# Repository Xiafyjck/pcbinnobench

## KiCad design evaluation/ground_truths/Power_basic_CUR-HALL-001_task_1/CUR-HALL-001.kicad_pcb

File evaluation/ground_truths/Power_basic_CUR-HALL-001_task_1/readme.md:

# CUR-HALL-001: Hall Effect Current Sensor Front-End Board

Uses ACS712 and OPA333 for current sensing, powered by 5V, but output voltage does not exceed 3.3V, ±20A range.

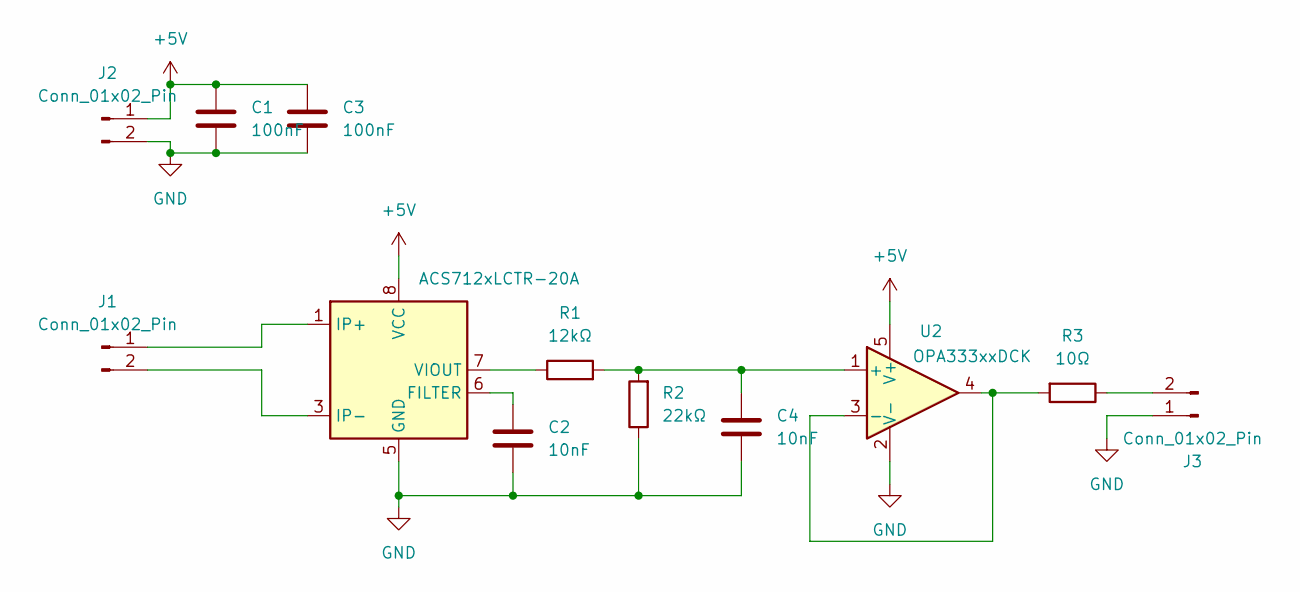
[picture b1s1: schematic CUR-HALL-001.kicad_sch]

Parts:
C1, C3: 100nF; C_0805_2012Metric
C2, C4: 10nF; C_0805_2012Metric
J1: Conn_01x02_Pin; Samtec_HPM-02-01-x-S_Straight_1x02_Pitch5.08mm
J2, J3: Conn_01x02_Pin; JST_EH_B2B-EH-A_1x02_P2.50mm_Vertical
R1: 12kΩ; R_0805_2012Metric
R2: 22kΩ; R_0805_2012Metric
R3: 10Ω; R_0805_2012Metric
U1: ACS712xLCTR-20A; SOIC-8_3.9x4.9mm_P1.27mm
U2: OPA333xxDCK; SOT-353_SC-70-5

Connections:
+5V: C1.1, C3.1, J2.1, U1.8 (VCC), U2.5 (V+)
GND: C1.2, C2.2, C3.2, C4.2, J2.2, J3.1, R2.1, U1.5 (GND), U2.2 (V-)
unnamed: J1.1, U1.1 (IP+), U1.2 (IP+)
unnamed: J1.2, U1.3 (IP-), U1.4 (IP-)
unnamed: J3.2, R3.1
unnamed: C2.1, U1.6 (FILTER)
unnamed: R1.1, U1.7 (VIOUT)
unnamed: C4.1, R1.2, R2.2, U2.1 (+)
unnamed: R3.2, U2.3 (-), U2.4

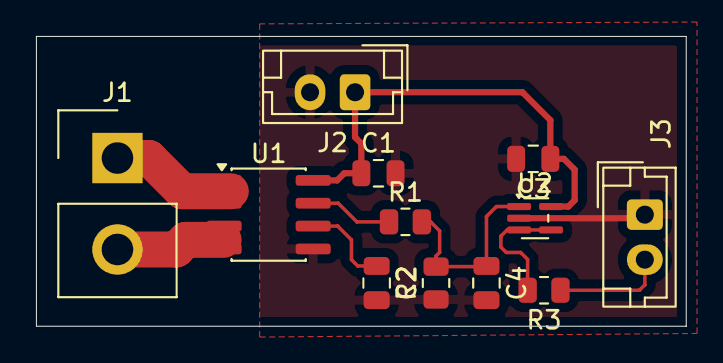
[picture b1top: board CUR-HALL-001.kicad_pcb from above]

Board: 2 copper layers, 36.1 x 16.1 mm, 12 parts (0 on the bottom side), 9 nets.

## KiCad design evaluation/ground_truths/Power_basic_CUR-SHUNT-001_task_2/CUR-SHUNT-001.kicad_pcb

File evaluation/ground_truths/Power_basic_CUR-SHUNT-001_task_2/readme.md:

# INA282 Low-Side Current Sensing

Use INA282 with 1.65V offset for current sensing.

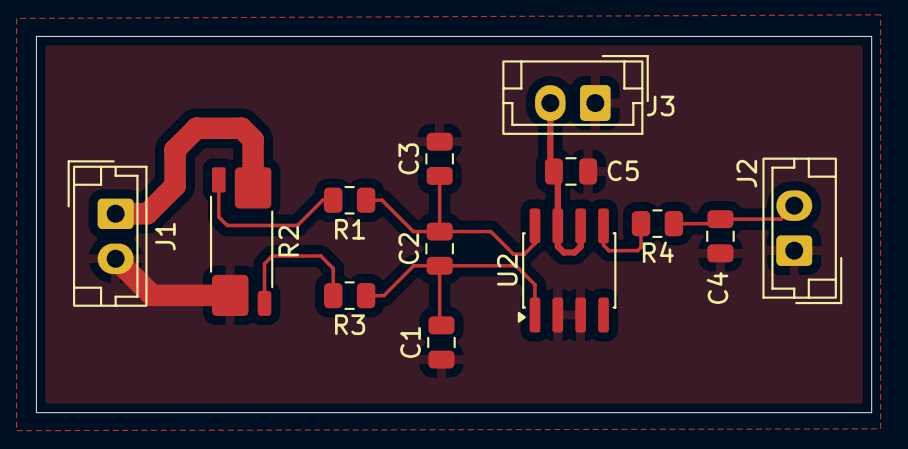
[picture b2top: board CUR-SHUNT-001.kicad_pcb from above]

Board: 2 copper layers, 46.4 x 20.9 mm, 13 parts (0 on the bottom side), 9 nets.

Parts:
C1, C2, C3: NC; C_0805_2012Metric
C4: 1nF; C_0805_2012Metric
C5: 100nF; C_0805_2012Metric
J1, J2, J3: Conn_01x02_Pin; JST_EH_B2B-EH-A_1x02_P2.50mm_Vertical
R1, R3, R4: 10Ω; R_0805_2012Metric
R2: R_Shunt; R_Shunt_Vishay_WSK2512_6332Metric_T1.19mm
U2: INA282; SOIC-8_3.9x4.9mm_P1.27mm

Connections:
+3.3V: C5.2, J3.2, U2.6 (V+), U2.7 (REF1)
GND: C1.1, C3.2, C4.1, C5.1, J1.2, J2.1, J3.1, R2.4, U2.2 (GND), U2.3 (REF2)
unnamed: J1.1, R2.1
unnamed: C4.2, J2.2, R4.1
unnamed: R1.2, R2.2
unnamed: R2.3, R3.2
unnamed: R4.2, U2.5
unnamed: C2.2, C3.1, R1.1, U2.8 (+)
unnamed: C1.2, C2.1, R3.1, U2.1 (-)

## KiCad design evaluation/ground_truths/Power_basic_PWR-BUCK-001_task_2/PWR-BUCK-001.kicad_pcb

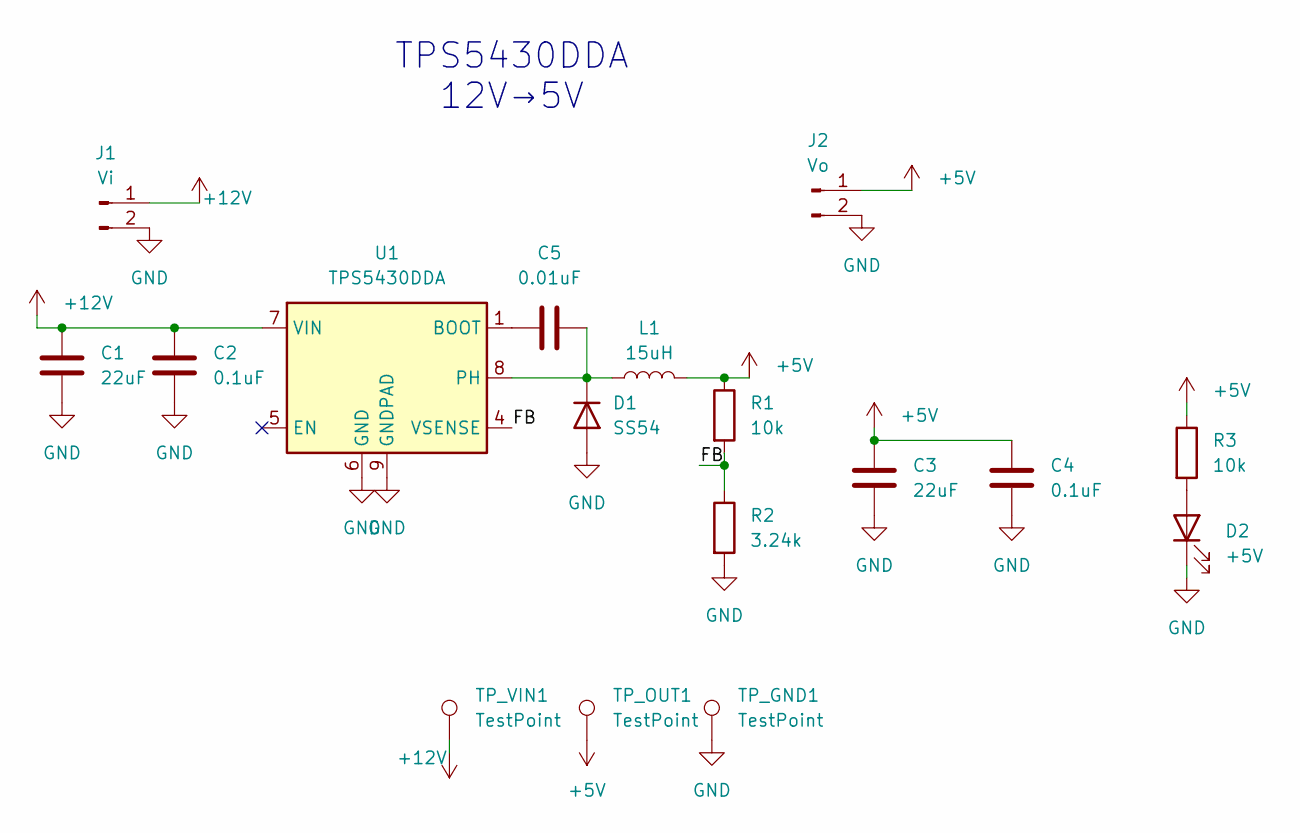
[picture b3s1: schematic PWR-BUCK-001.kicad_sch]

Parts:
C1, C3: 22uF; C_1206_3216Metric
C2, C4: 0.1uF; C_0805_2012Metric
C5: 0.01uF; C_0805_2012Metric
D1: SS54; D_SMB
D2: +5V; LED_0805_2012Metric
J1: Vi; JST_XH_B2B-XH-AM_1x02_P2.50mm_Vertical
J2: Vo; JST_XH_B2B-XH-AM_1x02_P2.50mm_Vertical
L1: 15uH; L_6.3x6.3_H3
R1, R3: 10k; R_0805_2012Metric
R2: 3.24k; R_0805_2012Metric
TP_GND1: TestPoint; TestPoint_Pad_D2.0mm
TP_OUT1: TestPoint; TestPoint_Pad_D2.0mm
TP_VIN1: TestPoint; TestPoint_Pad_D2.0mm
U1: TPS5430DDA; TI_SO-PowerPAD-8_ThermalVias

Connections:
+5V: C3.1, C4.1, J2.1, L1.2, R1.1, R3.1, TP_OUT1.1
+12V: C1.1, C2.1, J1.1, TP_VIN1.1, U1.7 (VIN)
/FB: R1.2, R2.1, U1.4 (VSENSE)
GND: C1.2, C2.2, C3.2, C4.2, D1.2 (A), D2.1 (K), J1.2, J2.2, R2.2, TP_GND1.1, U1.6 (GND), U1.9 (GNDPAD)
unnamed: C5.2, D1.1 (K), L1.1, U1.8 (PH)
unnamed: D2.2 (A), R3.2
unnamed: C5.1, U1.1 (BOOT)

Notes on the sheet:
TPS5430DDA 12V→5V

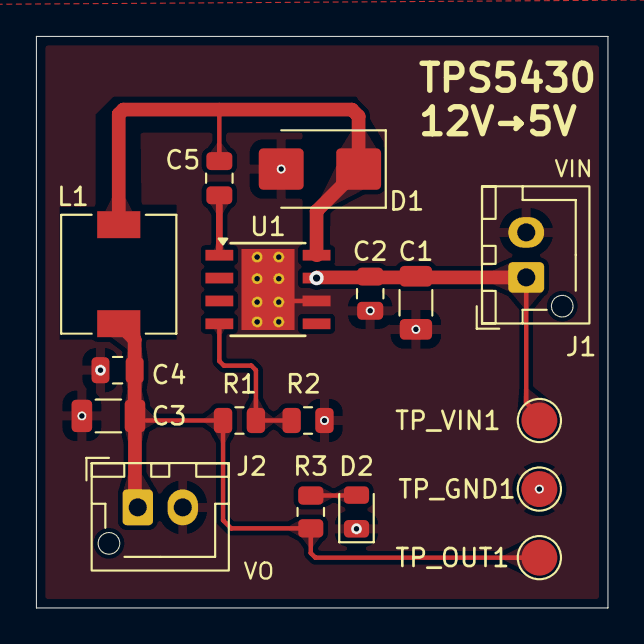
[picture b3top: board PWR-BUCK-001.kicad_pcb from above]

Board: 2 copper layers, 31.8 x 31.8 mm, 17 parts (0 on the bottom side), 7 nets.

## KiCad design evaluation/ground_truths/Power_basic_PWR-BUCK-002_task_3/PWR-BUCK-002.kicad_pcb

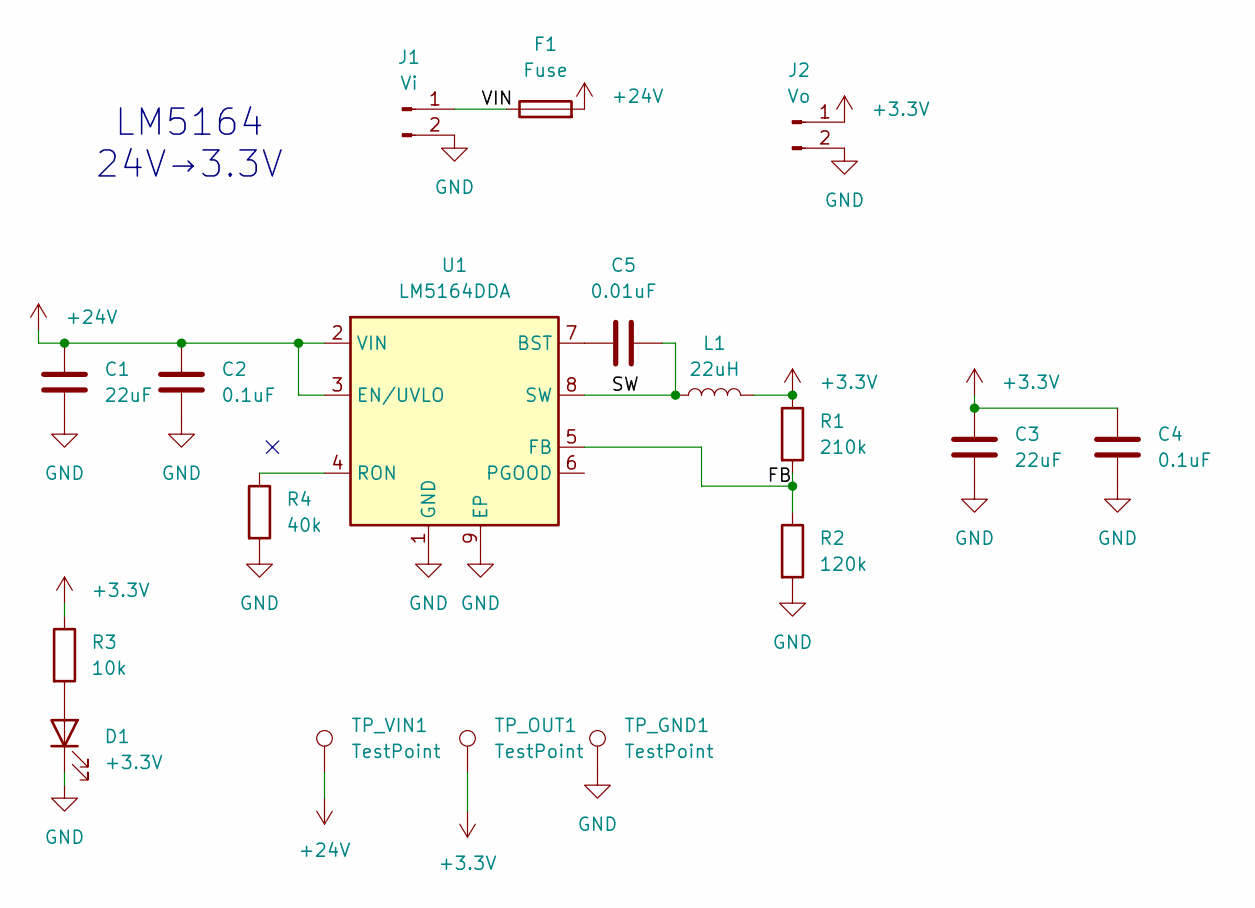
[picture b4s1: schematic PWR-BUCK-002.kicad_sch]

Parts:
C1, C3: 22uF; C_1206_3216Metric
C2, C4: 0.1uF; C_0805_2012Metric
C5: 0.01uF; C_0805_2012Metric
D1: +3.3V; LED_0805_2012Metric
F1: Fuse; Fuse_1210_3225Metric
J1: Vi; JST_XH_B2B-XH-AM_1x02_P2.50mm_Vertical
J2: Vo; JST_XH_B2B-XH-AM_1x02_P2.50mm_Vertical
L1: 22uH; L_6.3x6.3_H3
R1: 210k; R_0805_2012Metric
R2: 120k; R_0805_2012Metric
R3: 10k; R_0805_2012Metric
R4: 40k; R_0805_2012Metric
TP_GND1: TestPoint; TestPoint_Pad_D2.0mm
TP_OUT1: TestPoint; TestPoint_Pad_D2.0mm
TP_VIN1: TestPoint; TestPoint_Pad_D2.0mm
U1: LM5164DDA; HSOP-8-1EP_3.9x4.9mm_P1.27mm_EP2.41x3.1mm_ThermalVias

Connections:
+3.3V: C3.1, C4.1, J2.1, L1.2, R1.1, R3.1, TP_OUT1.1
+24V: C1.1, C2.1, F1.2, TP_VIN1.1, U1.2 (VIN), U1.3 (EN/UVLO)
/FB: R1.2, R2.1, U1.5 (FB)
/SW: C5.1, L1.1, U1.8 (SW)
/VIN: F1.1, J1.1
GND: C1.2, C2.2, C3.2, C4.2, D1.1 (K), J1.2, J2.2, R2.2, R4.2, TP_GND1.1, U1.1 (GND), U1.9 (EP)
unnamed: D1.2 (A), R3.2
unnamed: C5.2, U1.7 (BST)
unnamed: R4.1, U1.4 (RON)

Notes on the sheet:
LM5164 24V→3.3V

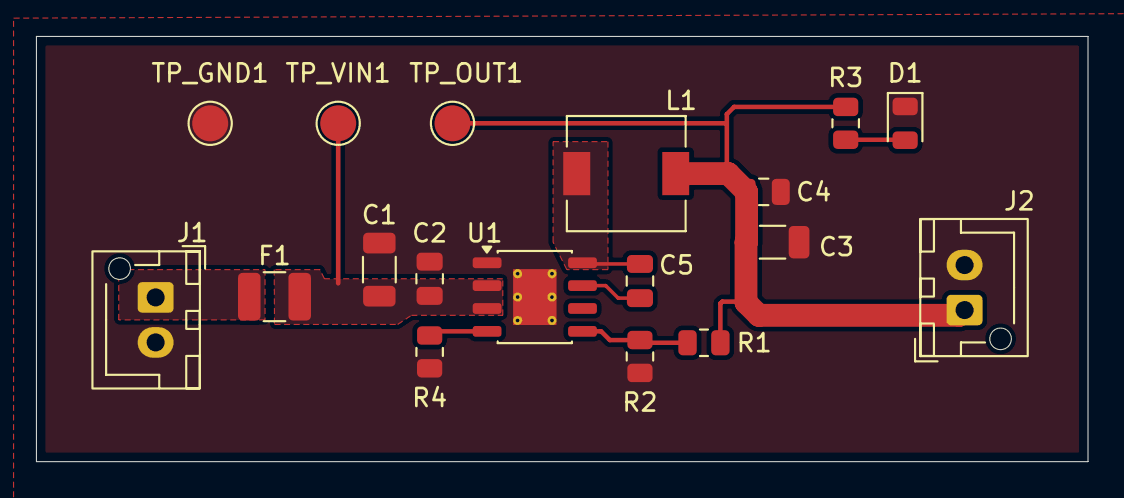
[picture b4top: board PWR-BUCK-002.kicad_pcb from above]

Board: 2 copper layers, 58.4 x 23.6 mm, 18 parts (0 on the bottom side), 9 nets.

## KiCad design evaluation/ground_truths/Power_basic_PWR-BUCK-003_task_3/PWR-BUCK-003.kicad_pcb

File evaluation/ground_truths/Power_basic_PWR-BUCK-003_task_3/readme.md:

# TPS562202

Design parameters: 5V input, 1.8V output

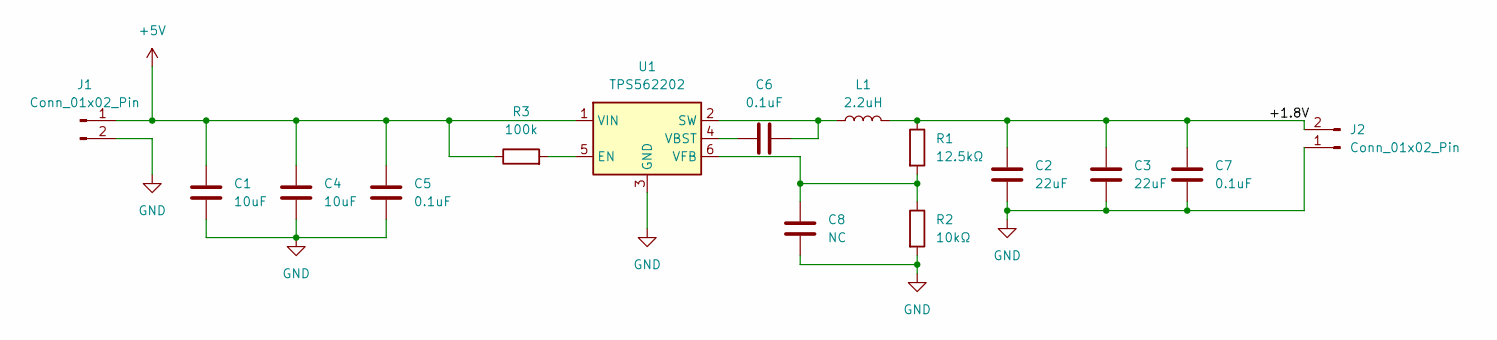
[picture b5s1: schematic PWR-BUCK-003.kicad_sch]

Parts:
C1, C4: 10uF; C_0805_2012Metric
C2, C3: 22uF; C_0805_2012Metric
C5, C6, C7: 0.1uF; C_0805_2012Metric
C8: NC; C_0805_2012Metric
J1, J2: Conn_01x02_Pin; JST_EH_B2B-EH-A_1x02_P2.50mm_Vertical
L1: 2.2uH; L_10.4x10.4_H4.8
R1: 12.5kΩ; R_0805_2012Metric
R2: 10kΩ; R_0805_2012Metric
R3: 100k; R_0805_2012Metric
U1: TPS562202; SOT-563

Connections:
+5V: C1.1, C4.1, C5.1, J1.1, R3.1, U1.1 (VIN)
/+1.8V: C2.1, C3.1, C7.1, J2.2, L1.2, R1.1
GND: C1.2, C2.2, C3.2, C4.2, C5.2, C7.2, C8.2, J1.2, J2.1, R2.2, U1.3 (GND)
unnamed: R3.2, U1.5 (EN)
unnamed: C6.2, L1.1, U1.2 (SW)
unnamed: C6.1, U1.4 (VBST)
unnamed: C8.1, R1.2, R2.1, U1.6 (VFB)

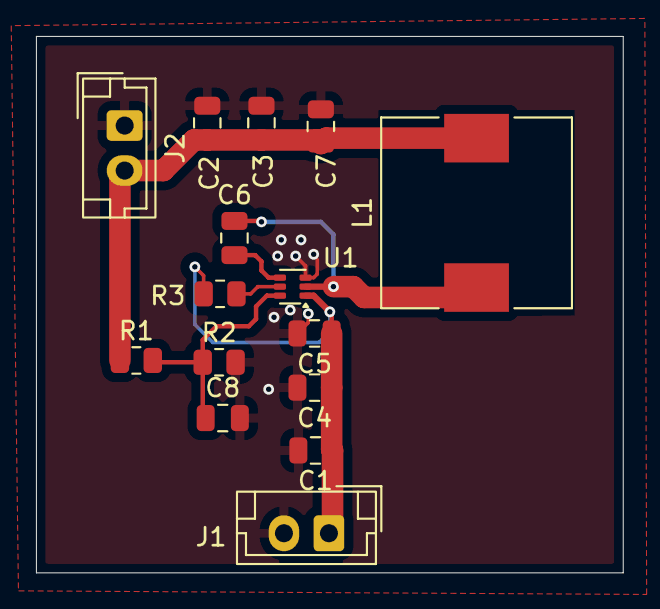
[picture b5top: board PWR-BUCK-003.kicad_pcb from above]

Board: 2 copper layers, 32.6 x 29.8 mm, 15 parts (0 on the bottom side), 7 nets.

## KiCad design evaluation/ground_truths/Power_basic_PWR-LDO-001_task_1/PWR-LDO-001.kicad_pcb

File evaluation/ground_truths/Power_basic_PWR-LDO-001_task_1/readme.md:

# PWR-LDO-001

5V to 3.3V LDO Digital Power Board, used to generate 3.3V digital power from 5V input.

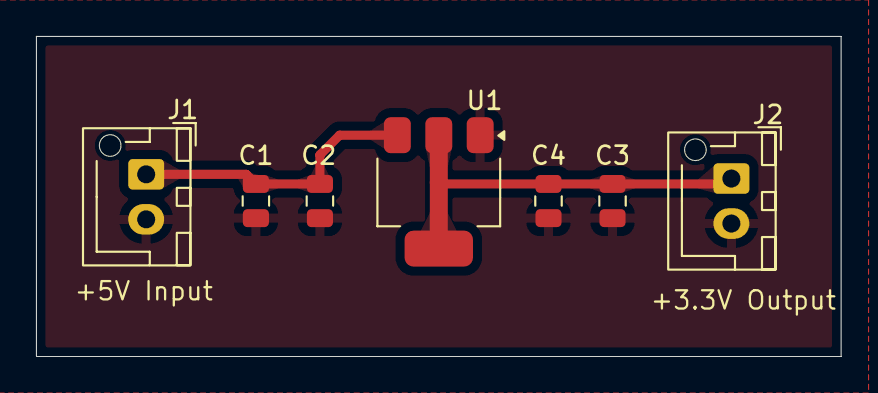
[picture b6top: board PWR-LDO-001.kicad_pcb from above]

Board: 2 copper layers, 44.7 x 17.8 mm, 7 parts (0 on the bottom side), 3 nets.

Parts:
C1, C3: 10uF; C_0805_2012Metric
C2, C4: 0.1uF; C_0805_2012Metric
J1: Vi; JST_XH_B2B-XH-AM_1x02_P2.50mm_Vertical
J2: Vo; JST_XH_B2B-XH-AM_1x02_P2.50mm_Vertical
U1: AMS1117-3.3; SOT-223-3_TabPin2

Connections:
+3.3V: C3.1, C4.1, J2.1, U1.2 (VO)
+5V: C1.1, C2.1, J1.1, U1.3 (VI)
GND: C1.2, C2.2, C3.2, C4.2, J1.2, J2.2, U1.1 (GND)

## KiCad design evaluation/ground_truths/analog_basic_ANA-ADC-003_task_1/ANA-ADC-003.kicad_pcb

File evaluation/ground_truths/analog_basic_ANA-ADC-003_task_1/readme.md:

# Differential Voltage Sampling Using ADS1115 and STM32F103C8

Sampling uses INA333, powered by 3.3V, REF3012 provides 1.2V reference voltage. Note that common-mode voltage must not exceed 3.3V, see INA333 datasheet for details.

Uses PB5, PB6, PB7 pins to communicate with ADS1115.

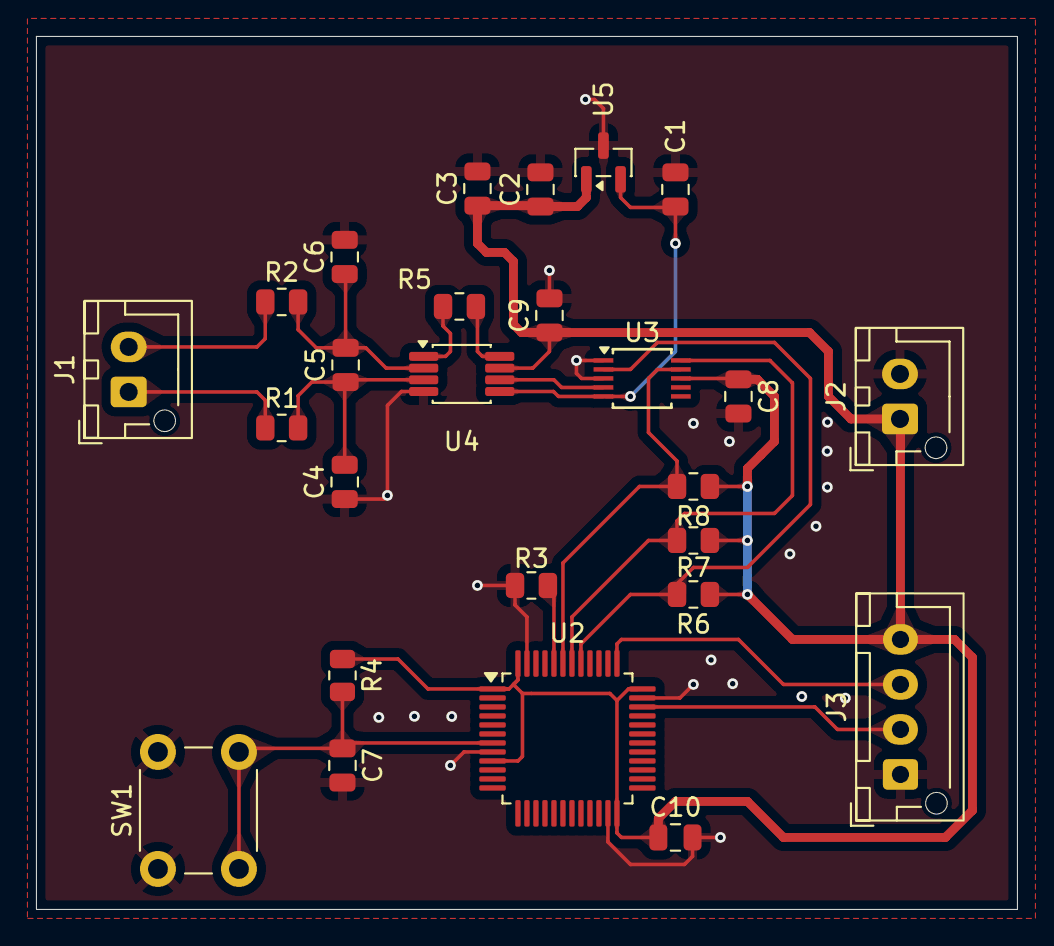
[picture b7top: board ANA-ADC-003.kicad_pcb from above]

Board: 2 copper layers, 54.5 x 48.5 mm, 26 parts (0 on the bottom side), 17 nets.

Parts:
C1: 10uF; C_0805_2012Metric
C2, C8, C9: 0.1uF; C_0805_2012Metric
C3: 1uF; C_0805_2012Metric
C4, C5, C6: 1nF; C_0805_2012Metric
C7, C10: 100nF; C_0805_2012Metric
J1, J2: Conn_01x02_Pin; JST_XH_B2B-XH-AM_1x02_P2.50mm_Vertical
J3: Conn_01x04_Pin; JST_XH_B4B-XH-AM_1x04_P2.50mm_Vertical
R1, R2, R3, R4, R6: 10k; R_0805_2012Metric
R5: 100k; R_0805_2012Metric
R7, R8: 4.7k; R_0805_2012Metric
SW1: SW_Push; SW_PUSH_6mm
U2: STM32F103C8Tx; LQFP-48_7x7mm_P0.5mm
U3: ADS1115IDGS; TSSOP-10_3x3mm_P0.5mm
U4: INA333xxDGK; VSSOP-8_3x3mm_P0.65mm
U5: REF3012; SOT-23

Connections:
+3.3V: C2.1, C3.1, C8.1, C9.1, C10.1, J2.1, J3.4, R4.1, R6.1, R7.1, R8.1, U2.1 (VBAT), U2.9 (VDDA), U2.24 (VDD), U2.36 (VDD), U2.48 (VDD), U3.8 (VDD), U4.7 (V+), U5.1 (IN)
/ADC_HIN: J1.1, R1.1
/ADC_LIN: J1.2, R2.1
/stm32/ADS_ALERT: R6.2, U2.41 (PB5), U3.2 (ALERT/RDY)
/stm32/BOOT0: R3.1, U2.44 (BOOT0)
/stm32/I2C1_SCL: R7.2, U2.42 (PB6), U3.10 (SCL)
/stm32/I2C1_SDA: R8.2, U2.43 (PB7), U3.9 (SDA)
/stm32/NRST: C7.1, R4.2, SW1.2, U2.7 (NRST)
/stm32/swclk: J3.3, U2.37 (PA14)
/stm32/swdio: J3.2, U2.34 (PA13)
/vref: C1.1, U3.5 (AIN1), U4.5 (Ref), U5.2 (OUT)
GND: C1.2, C2.2, C3.2, C4.1, C6.2, C7.2, C8.2, C9.2, C10.2, J2.2, J3.1, R3.2, SW1.1, U2.8 (VSSA), U2.23 (VSS), U2.35 (VSS), U2.47 (VSS), U3.1 (ADDR), U3.3 (GND), U4.4 (V-), U5.3 (GND)
unnamed: R5.1, U4.8 (Rg)
unnamed: R5.2, U4.1 (Rg)
unnamed: U3.4 (AIN0), U4.6
unnamed: C4.2, C5.1, R1.2, U4.3 (+)
unnamed: C5.2, C6.1, R2.2, U4.2 (-)
